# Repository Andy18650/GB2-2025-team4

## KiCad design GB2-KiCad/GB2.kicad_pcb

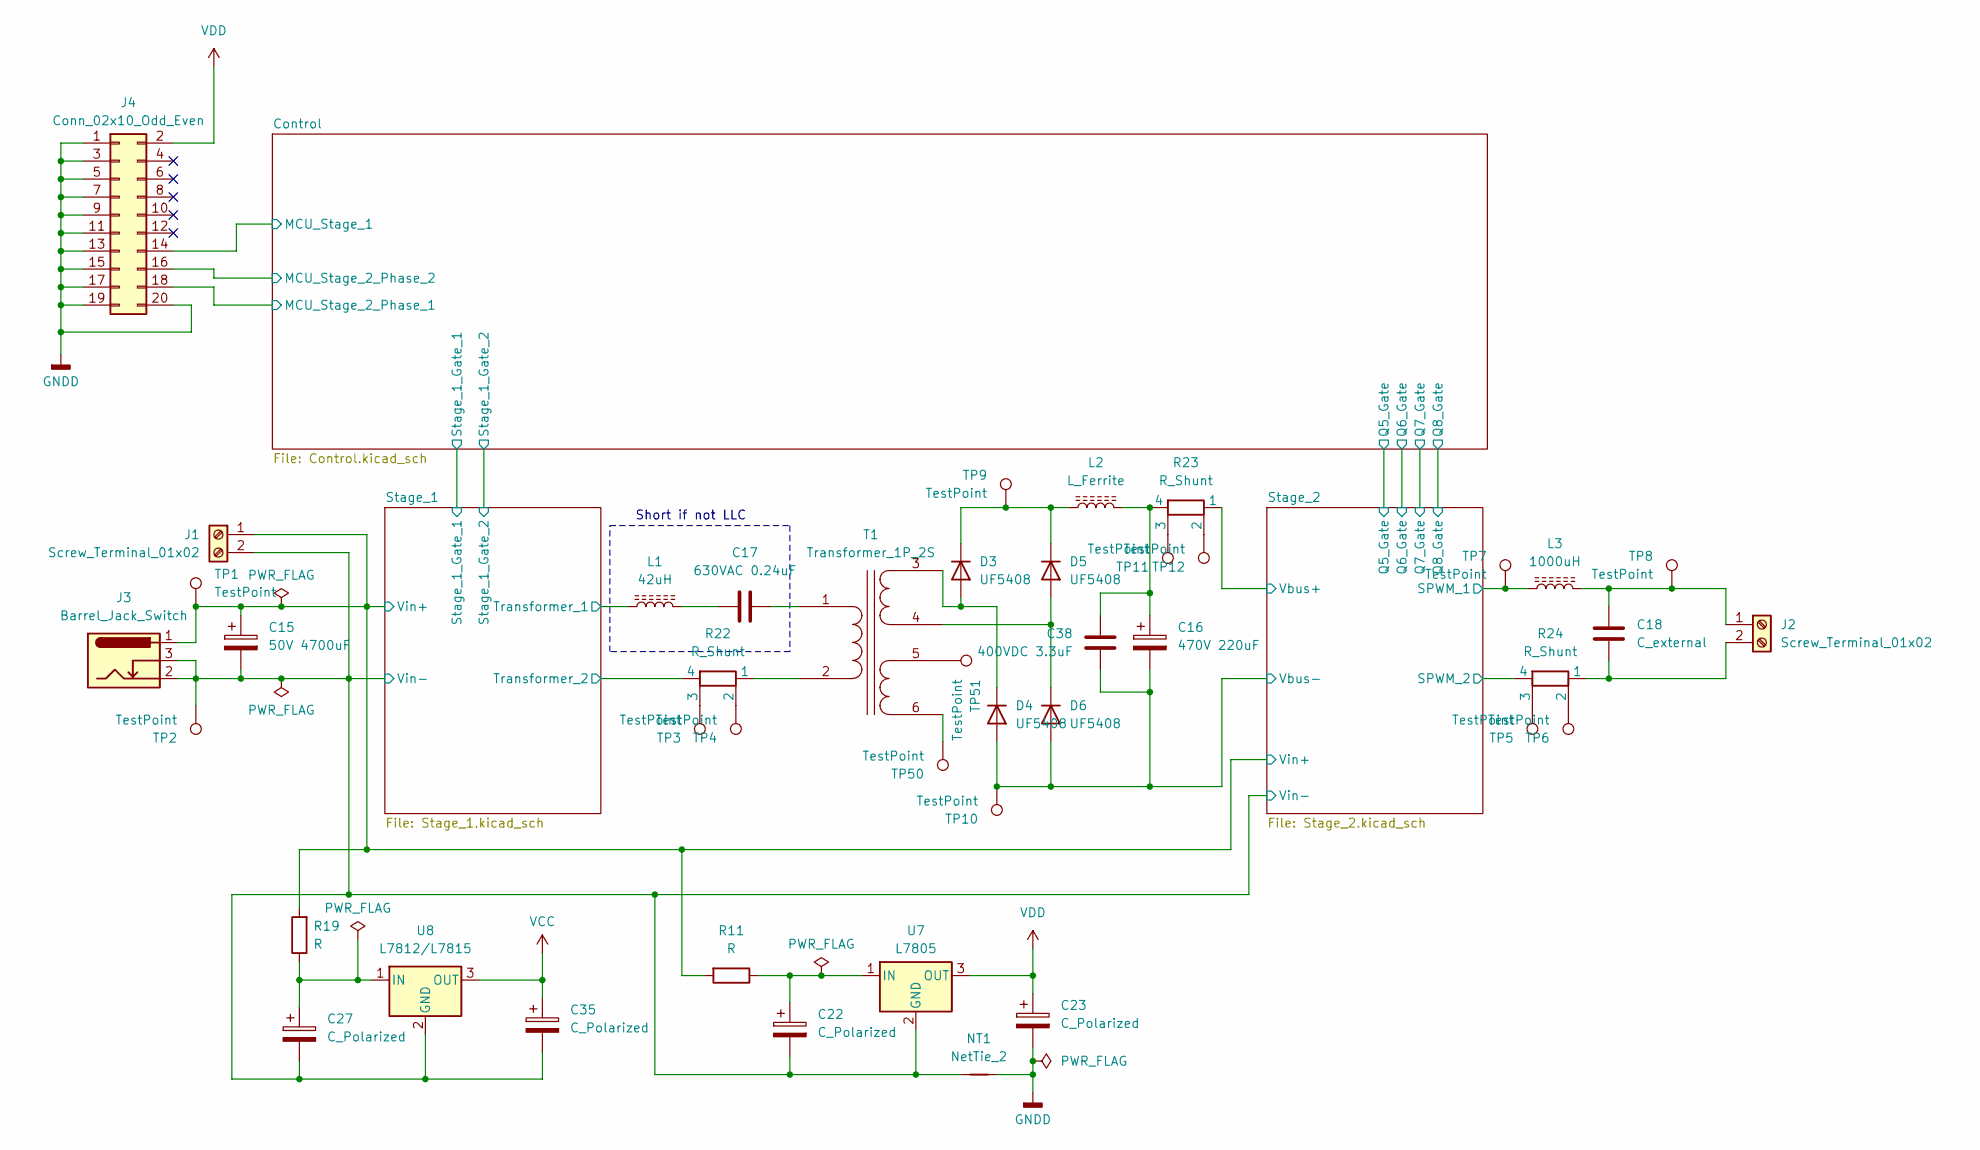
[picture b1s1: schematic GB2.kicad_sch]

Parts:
C15: 50V 4700uF; CP_Radial_D16.0mm_P7.50mm
C16: 470V 220uF; CP_Radial_D22.0mm_P10.00mm_SnapIn
C17: 630VAC 0.24uF; C_Rect_L33.0mm_W15.0mm_P27.50mm_MKS4
C18: C_external
C22, C23, C27, C35: C_Polarized; CP_Radial_D10.0mm_P2.50mm_P5.00mm
C38: 400VDC 3.3uF; C_Rect_L33.0mm_W15.0mm_P27.50mm_MKS4
D3, D4, D5, D6: UF5408; D_DO-201AD_P15.24mm_Horizontal
J1, J2: Screw_Terminal_01x02; TerminalBlock_Dinkle_DT-55-B01X-02_P10.00mm
J3: Barrel_Jack_Switch; BarrelJack_GCT_DCJ200-10-A_Horizontal
J4: Conn_02x10_Odd_Even; PinHeader_2x10_P2.54mm_Vertical
L1: 42uH; L_Toroid_Vertical_L21.6mm_W8.4mm_P8.38mm_Pulse_G
L2: L_Ferrite; L_Toroid_Vertical_L21.6mm_W8.4mm_P8.38mm_Pulse_G
L3: 1000uH; L_Toroid_Vertical_L21.6mm_W8.4mm_P8.38mm_Pulse_G
NT1: NetTie_2; NetTie-2_SMD_Pad2.0mm
R11, R19: R; R_Axial_DIN0204_L3.6mm_D1.6mm_P7.62mm_Horizontal
R22, R23, R24: R_Shunt; R_Axial_Shunt_L22.2mm_W8.0mm_PS14.30mm_P25.40mm
T1: Transformer_1P_2S; Transformer_GB2_Horizontal
TP1, TP2, TP3, TP4, TP5, TP6, TP7, TP8, TP9, TP10, TP11, TP12, TP50, TP51: TestPoint; Pin_D1.0mm_L10.0mm
U7: L7805; TO-220-3_Vertical
U8: L7812/L7815; TO-220-3_Vertical

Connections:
/Control/MCU_Stage_1: J4.14; also elsewhere on the board
/Control/MCU_Stage_2_Phase_1: J4.18; also elsewhere on the board
/Control/MCU_Stage_2_Phase_2: J4.16; also elsewhere on the board
/Stage_1/Transformer_1: L1.1; also elsewhere on the board
/Stage_1/Transformer_2: R22.4; also elsewhere on the board
/Stage_1/Vin+: C15.1, J1.1, J3.1, R11.2, R19.2, TP1.1; also elsewhere on the board
/Stage_1/Vin-: C15.2, C22.2, C27.2, C35.2, J1.2, J3.2, J3.3, NT1.1, TP2.1, U7.2 (GND), U8.2 (GND); also elsewhere on the board
/Stage_2/SPWM_1: L3.1, TP7.1; also elsewhere on the board
/Stage_2/SPWM_2: R24.4; also elsewhere on the board
/Stage_2/Vbus+: R23.1; also elsewhere on the board
/Stage_2/Vbus-: C16.2, C38.1, D4.2 (A), D6.2 (A), TP10.1; also elsewhere on the board
GNDD: C23.2, J4.1, J4.3, J4.5, J4.7, J4.9, J4.11, J4.13, J4.15, J4.17, J4.19, J4.20, NT1.2; also elsewhere on the board
unnamed: C16.1, C38.2, L2.2, R23.4
unnamed: C17.1, L1.2
unnamed: D3.2 (A), D4.1 (K), T1.3 (SA)
unnamed: D3.1 (K), D5.1 (K), L2.1, TP9.1
unnamed: D5.2 (A), D6.1 (K), T1.4 (SB)
unnamed: C18.2, J2.1, L3.2, TP8.1
unnamed: C18.1, J2.2, R24.1
unnamed: R22.2, TP4.1
unnamed: R22.3, TP3.1
unnamed: R23.2, TP12.1
unnamed: R23.3, TP11.1
unnamed: R24.2, TP6.1
unnamed: R24.3, TP5.1
unnamed: C17.2, T1.1 (AA)
unnamed: R22.1, T1.2 (AB)
unnamed: T1.5 (SC), TP51.1
unnamed: T1.6 (SD), TP50.1
unnamed: C22.1, R11.1, U7.1 (IN)
unnamed: C27.1, R19.1, U8.1 (IN)
VCC: C35.1, U8.3 (OUT); also elsewhere on the board
VDD: C23.1, J4.2, U7.3 (OUT); also elsewhere on the board

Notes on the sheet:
Short if not LLC

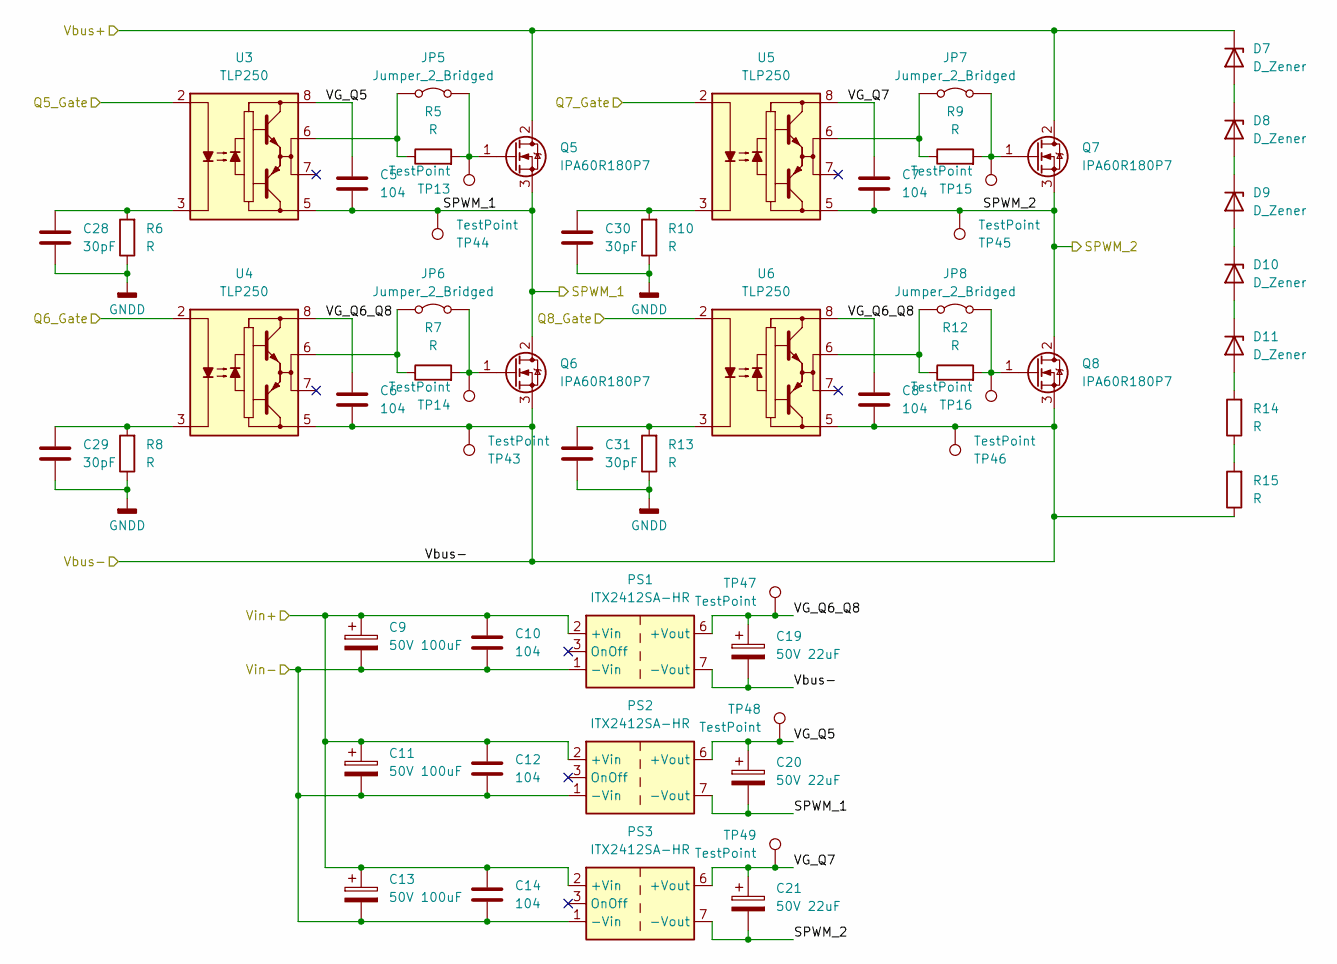
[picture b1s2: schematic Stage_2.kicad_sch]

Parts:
C5, C6, C7, C8, C10, C12, C14: 104; C_Disc_D7.0mm_W2.5mm_P5.00mm
C9, C11, C13: 50V 100uF; CP_Radial_D10.0mm_P2.50mm_P5.00mm
C19, C20, C21: 50V 22uF; CP_Radial_D5.0mm_P2.00mm
C28, C29, C30, C31: 30pF; C_Disc_D3.4mm_W2.1mm_P2.50mm
D7, D8, D9, D10, D11: D_Zener; D_DO-41_SOD81_P10.16mm_Horizontal
JP5, JP6, JP7, JP8: Jumper_2_Bridged; SolderJumper-2_P1.3mm_Bridged_Pad1.0x1.5mm
PS1, PS2, PS3: ITX2412SA-HR; Converter_DCDC_XP_POWER-ITxxxxxS_THT
Q5, Q6, Q7, Q8: IPA60R180P7; TO-220-3_Vertical
R5, R6, R7, R8, R9, R10, R12, R13, R14, R15: R; R_Axial_DIN0204_L3.6mm_D1.6mm_P7.62mm_Horizontal
TP13, TP14, TP15, TP16, TP43, TP44, TP45, TP46, TP47, TP48, TP49: TestPoint; Pin_D1.0mm_L10.0mm
U3, U4, U5, U6: TLP250; DIP-8_W7.62mm

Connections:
/Control/Q5_Gate: U3.2 (A); also elsewhere on the board
/Control/Q6_Gate: U4.2 (A); also elsewhere on the board
/Control/Q7_Gate: U5.2 (A); also elsewhere on the board
/Control/Q8_Gate: U6.2 (A); also elsewhere on the board
/Stage_1/Vin+: C9.1, C10.1, C11.1, C12.1, C13.1, C14.1, PS1.2 (+Vin), PS2.2 (+Vin), PS3.2 (+Vin); also elsewhere on the board
/Stage_1/Vin-: C9.2, C10.2, C11.2, C12.2, C13.2, C14.2, PS1.1 (-Vin), PS2.1 (-Vin), PS3.1 (-Vin); also elsewhere on the board
/Stage_2/SPWM_1: C5.2, C20.2, PS2.7 (-Vout), Q5.3 (S), Q6.2 (D), TP44.1, U3.5 (VEE); also elsewhere on the board
/Stage_2/SPWM_2: C7.2, C21.2, PS3.7 (-Vout), Q7.3 (S), Q8.2 (D), TP45.1, U5.5 (VEE); also elsewhere on the board
/Stage_2/VG_Q5: C5.1, C20.1, PS2.6 (+Vout), TP48.1, U3.8 (VCC)
/Stage_2/VG_Q6_Q8: C6.1, C8.1, C19.1, PS1.6 (+Vout), TP47.1, U4.8 (VCC), U6.8 (VCC)
/Stage_2/VG_Q7: C7.1, C21.1, PS3.6 (+Vout), TP49.1, U5.8 (VCC)
/Stage_2/Vbus+: D7.1 (K), Q5.2 (D), Q7.2 (D); also elsewhere on the board
/Stage_2/Vbus-: C6.2, C8.2, C19.2, PS1.7 (-Vout), Q6.3 (S), Q8.3 (S), R15.1, TP43.1, TP46.1, U4.5 (VEE), U6.5 (VEE); also elsewhere on the board
GNDD: C28.2, C29.2, C30.2, C31.2, R6.1, R8.1, R10.1, R13.1; also elsewhere on the board
unnamed: D7.2 (A), D8.1 (K)
unnamed: D8.2 (A), D9.1 (K)
unnamed: D10.2 (A), D11.1 (K)
unnamed: D9.2 (A), D10.1 (K)
unnamed: D11.2 (A), R14.2
unnamed: JP5.1 (A), R5.1, U3.6 (VO)
unnamed: JP5.2 (B), Q5.1 (G), R5.2, TP13.1
unnamed: JP6.1 (A), R7.1, U4.6 (VO)
unnamed: JP6.2 (B), Q6.1 (G), R7.2, TP14.1
unnamed: JP7.1 (A), R9.1, U5.6 (VO)
unnamed: JP7.2 (B), Q7.1 (G), R9.2, TP15.1
unnamed: JP8.1 (A), R12.1, U6.6 (VO)
unnamed: JP8.2 (B), Q8.1 (G), R12.2, TP16.1
unnamed: R14.1, R15.2
unnamed: C28.1, R6.2, U3.3 (C)
unnamed: C29.1, R8.2, U4.3 (C)
unnamed: C30.1, R10.2, U5.3 (C)
unnamed: C31.1, R13.2, U6.3 (C)

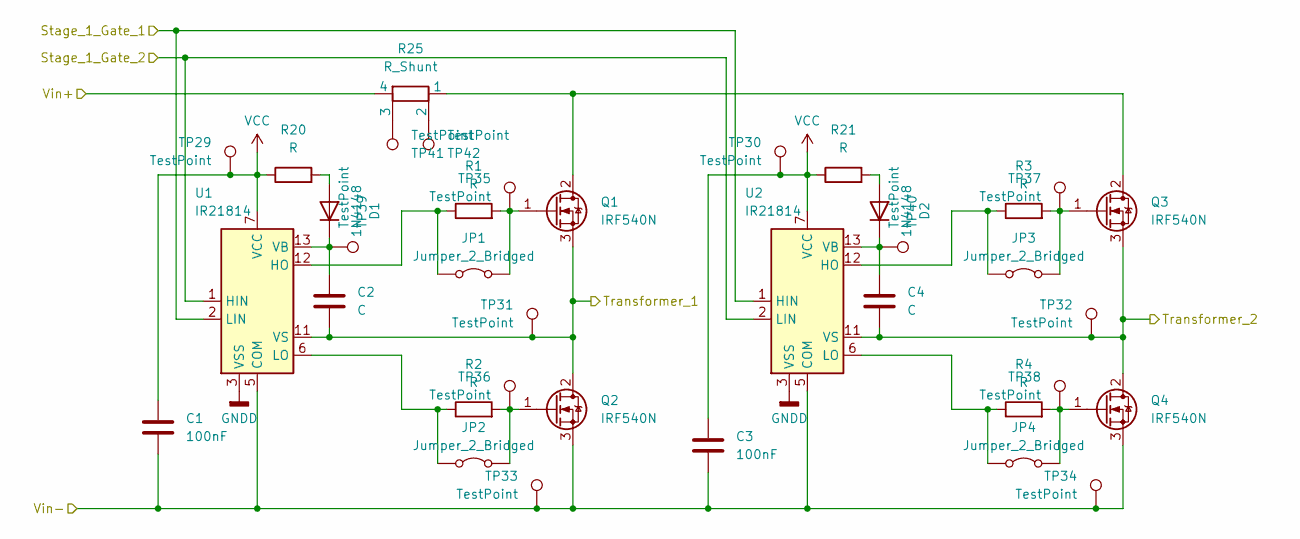
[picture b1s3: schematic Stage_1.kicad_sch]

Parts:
C1, C3: 100nF; C_Disc_D7.0mm_W2.5mm_P5.00mm
C2, C4: C; C_Disc_D7.0mm_W2.5mm_P5.00mm
D1, D2: 1N4148; D_DO-35_SOD27_P10.16mm_Horizontal
JP1, JP2, JP3, JP4: Jumper_2_Bridged; SolderJumper-2_P1.3mm_Bridged_Pad1.0x1.5mm
Q1, Q2, Q3, Q4: IRF540N; TO-220-3_Vertical
R1, R2, R3, R4, R20, R21: R; R_Axial_DIN0204_L3.6mm_D1.6mm_P7.62mm_Horizontal
R25: R_Shunt; R_Axial_Shunt_L22.2mm_W8.0mm_PS14.30mm_P25.40mm
TP29, TP30, TP31, TP32, TP33, TP34, TP35, TP36, TP37, TP38, TP39, TP40, TP41, TP42: TestPoint; Pin_D1.0mm_L10.0mm
U1, U2: IR21814; DIP-14_W7.62mm_Socket

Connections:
/Control/Stage_1_Gate_1: U1.2 (LIN), U2.1 (HIN); also elsewhere on the board
/Control/Stage_1_Gate_2: U1.1 (HIN), U2.2 (LIN); also elsewhere on the board
/Stage_1/Transformer_1: C2.2, Q1.3 (S), Q2.2 (D), TP31.1, U1.11 (VS); also elsewhere on the board
/Stage_1/Transformer_2: C4.2, Q3.3 (S), Q4.2 (D), TP32.1, U2.11 (VS); also elsewhere on the board
/Stage_1/Vin+: R25.4; also elsewhere on the board
/Stage_1/Vin-: C1.2, C3.2, Q2.3 (S), Q4.3 (S), TP33.1, TP34.1, U1.5 (COM), U2.5 (COM); also elsewhere on the board
GNDD: U1.3 (VSS), U2.3 (VSS); also elsewhere on the board
unnamed: D1.2 (A), R20.2
unnamed: C2.1, D1.1 (K), TP39.1, U1.13 (VB)
unnamed: D2.2 (A), R21.2
unnamed: C4.1, D2.1 (K), TP40.1, U2.13 (VB)
unnamed: JP1.1 (A), R1.1, U1.12 (HO)
unnamed: JP1.2 (B), Q1.1 (G), R1.2, TP35.1
unnamed: JP2.1 (A), R2.1, U1.6 (LO)
unnamed: JP2.2 (B), Q2.1 (G), R2.2, TP36.1
unnamed: JP3.1 (A), R3.1, U2.12 (HO)
unnamed: JP3.2 (B), Q3.1 (G), R3.2, TP37.1
unnamed: JP4.1 (A), R4.1, U2.6 (LO)
unnamed: JP4.2 (B), Q4.1 (G), R4.2, TP38.1
unnamed: Q1.2 (D), Q3.2 (D), R25.1
unnamed: R25.2, TP42.1
unnamed: R25.3, TP41.1
VCC: C1.1, C3.1, R20.1, R21.1, TP29.1, TP30.1, U1.7 (VCC), U2.7 (VCC); also elsewhere on the board

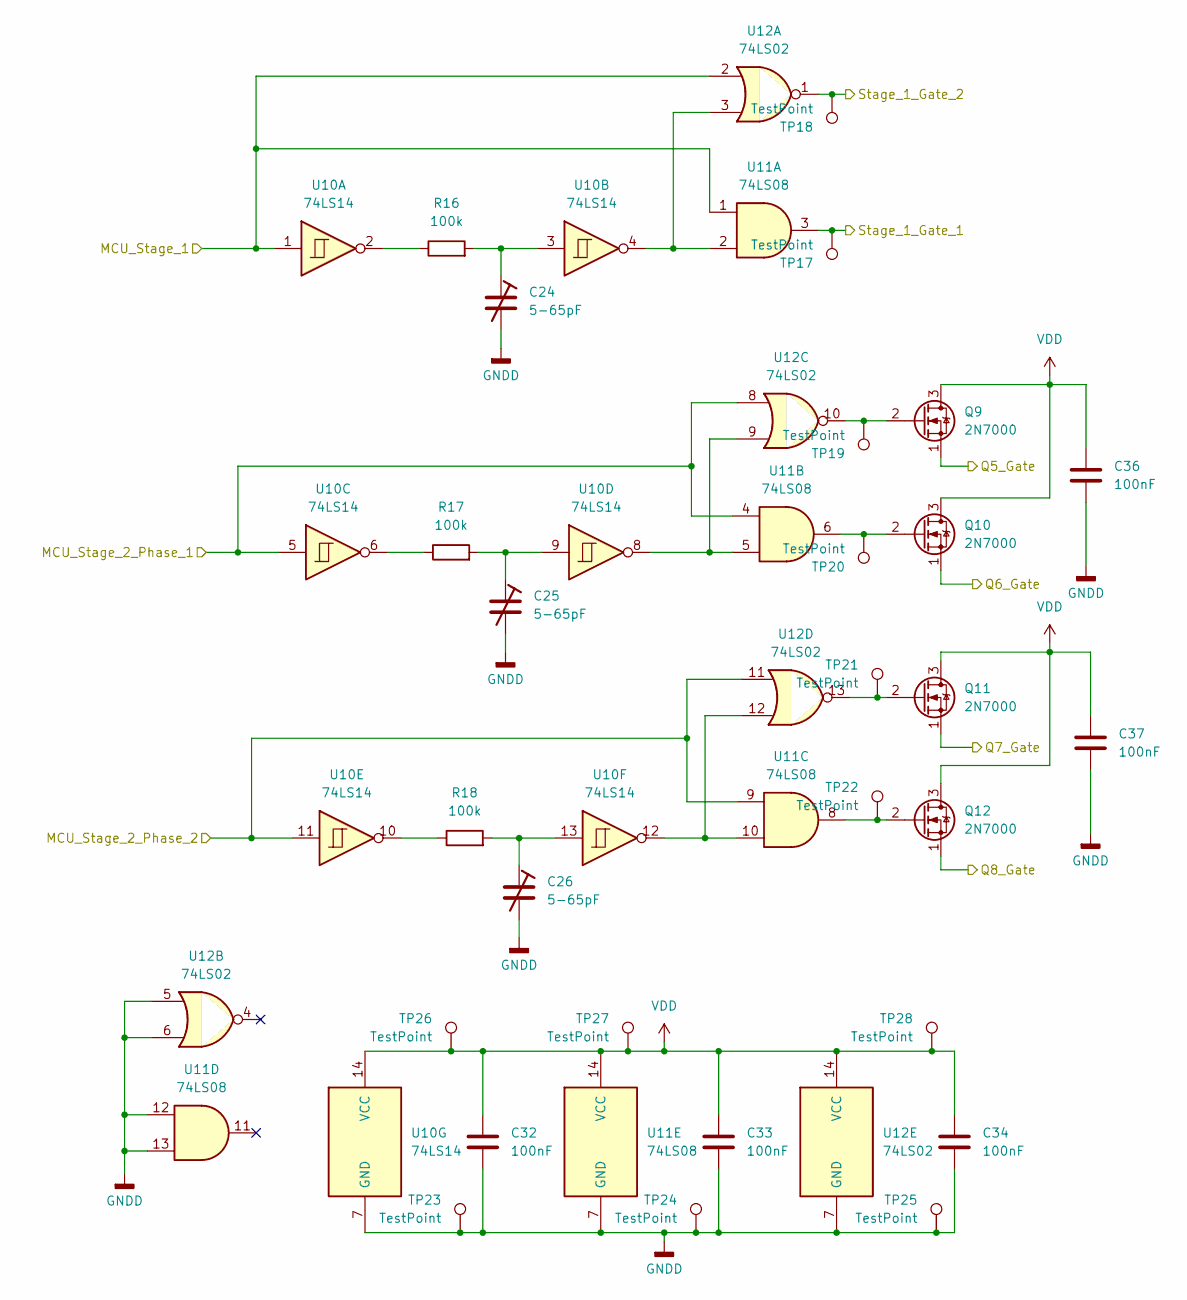
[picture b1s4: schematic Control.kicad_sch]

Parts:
C24, C25, C26: 5-65pF; C_Trim
C32, C33, C34, C36, C37: 100nF; C_Disc_D7.0mm_W2.5mm_P5.00mm
Q9, Q10, Q11, Q12: 2N7000; TO-92L_HandSolder
R16, R17, R18: 100k; R_Axial_DIN0204_L3.6mm_D1.6mm_P7.62mm_Horizontal
TP17, TP18, TP19, TP20, TP21, TP22, TP23, TP24, TP25, TP26, TP27, TP28: TestPoint; Pin_D1.0mm_L10.0mm
U10: 74LS14; DIP-14_W7.62mm_Socket
U11: 74LS08; DIP-14_W7.62mm_Socket
U12: 74LS02; DIP-14_W7.62mm_Socket

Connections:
/Control/MCU_Stage_1: U10.1, U11.1, U12.2; also elsewhere on the board
/Control/MCU_Stage_2_Phase_1: U10.5, U11.4, U12.8; also elsewhere on the board
/Control/MCU_Stage_2_Phase_2: U10.11, U11.9, U12.11; also elsewhere on the board
/Control/Q5_Gate: Q9.1 (S); also elsewhere on the board
/Control/Q6_Gate: Q10.1 (S); also elsewhere on the board
/Control/Q7_Gate: Q11.1 (S); also elsewhere on the board
/Control/Q8_Gate: Q12.1 (S); also elsewhere on the board
/Control/Stage_1_Gate_1: TP17.1, U11.3; also elsewhere on the board
/Control/Stage_1_Gate_2: TP18.1, U12.1; also elsewhere on the board
GNDD: C24.2, C25.2, C26.2, C32.2, C33.2, C34.2, C36.2, C37.2, TP23.1, TP24.1, TP25.1, U10.7 (GND), U11.7 (GND), U11.12, U11.13, U12.5, U12.6, U12.7 (GND); also elsewhere on the board
unnamed: C24.1, R16.2, U10.3
unnamed: C25.1, R17.2, U10.9
unnamed: C26.1, R18.2, U10.13
unnamed: Q9.2 (G), TP19.1, U12.10
unnamed: Q10.2 (G), TP20.1, U11.6
unnamed: Q11.2 (G), TP21.1, U12.13
unnamed: Q12.2 (G), TP22.1, U11.8
unnamed: R16.1, U10.2
unnamed: R17.1, U10.6
unnamed: R18.1, U10.10
unnamed: U10.4, U11.2, U12.3
unnamed: U10.8, U11.5, U12.9
unnamed: U10.12, U11.10, U12.12
VDD: C32.1, C33.1, C34.1, C36.1, C37.1, Q9.3 (D), Q10.3 (D), Q11.3 (D), Q12.3 (D), TP26.1, TP27.1, TP28.1, U10.14 (VCC), U11.14 (VCC), U12.14 (VCC); also elsewhere on the board

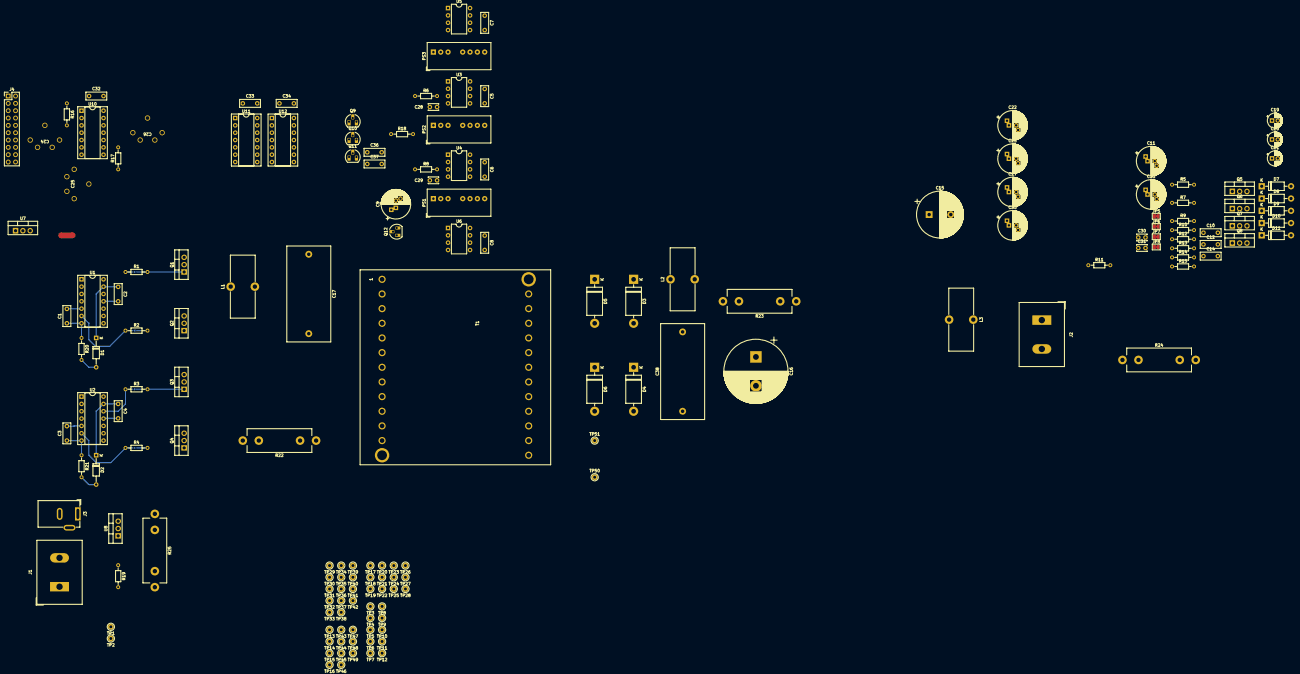
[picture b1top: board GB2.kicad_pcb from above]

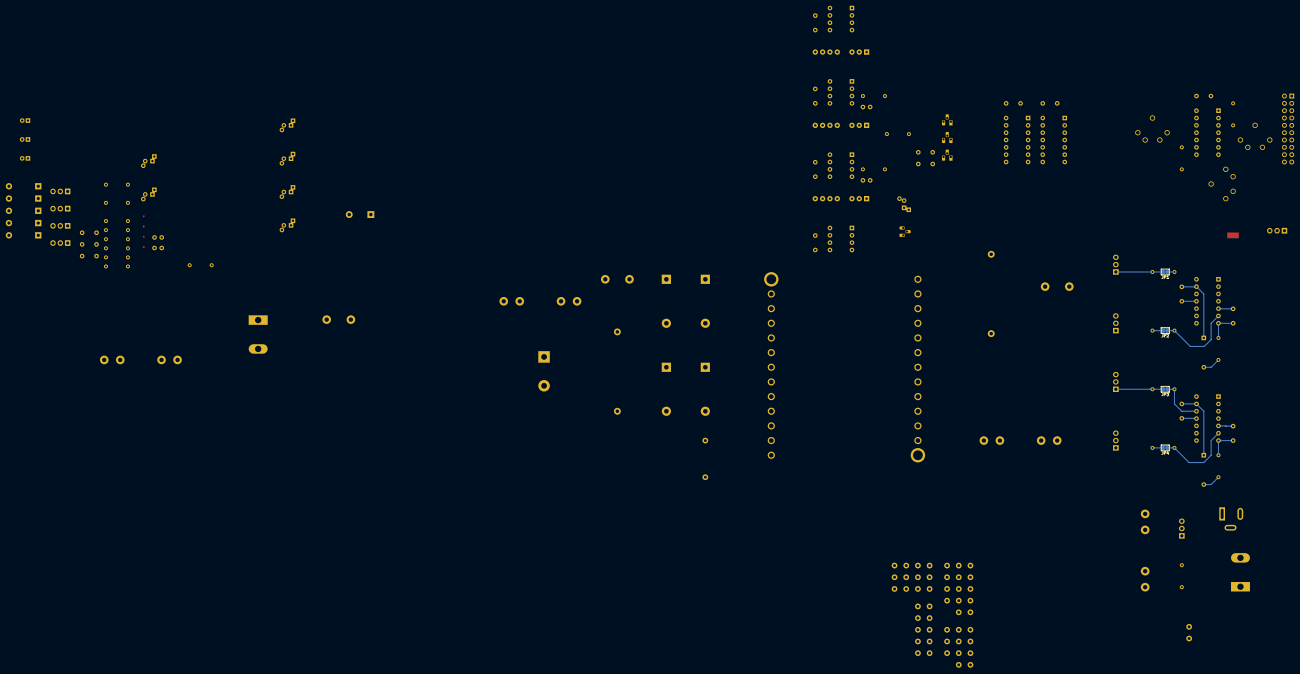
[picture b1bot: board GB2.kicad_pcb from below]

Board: 2 copper layers, 167 parts (4 on the bottom side), 88 nets.

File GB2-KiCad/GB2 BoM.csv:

"Reference","Value","Datasheet","Footprint","Qty","DNP"
"C1,C3,C32,C33,C34,C36,C37","100nF","~","Capacitor_THT:C_Disc_D7.0mm_W2.5mm_P5.00mm","7",""
"C2,C4","C","~","Capacitor_THT:C_Disc_D7.0mm_W2.5mm_P5.00mm","2",""
"C5,C6,C7,C8,C10,C12,C14","104","~","Capacitor_THT:C_Disc_D7.0mm_W2.5mm_P5.00mm","7",""
"C9,C11,C13","50V 100uF","~","Capacitor_THT:CP_Radial_D10.0mm_P2.50mm_P5.00mm","3",""
"C15","50V 4700uF","~","Capacitor_THT:CP_Radial_D16.0mm_P7.50mm","1",""
"C16","470V 220uF","~","Capacitor_THT:CP_Radial_D22.0mm_P10.00mm_SnapIn","1",""
"C18","C_external","~","","1",""
"C19,C20,C21","50V 22uF","~","Capacitor_THT:CP_Radial_D5.0mm_P2.00mm","3",""
"C22,C23,C27,C35","C_Polarized","~","Capacitor_THT:CP_Radial_D10.0mm_P2.50mm_P5.00mm","4",""
"C24,C25,C26","5-65pF","https://www.farnell.com/datasheets/3868946.pdf","GB2:C_Trim","3",""
"C28,C29,C30,C31","30pF","~","Capacitor_THT:C_Disc_D3.4mm_W2.1mm_P2.50mm","4",""
"C38","400VDC 3.3uF","~","Capacitor_THT:C_Rect_L33.0mm_W15.0mm_P27.50mm_MKS4","1",""
"D1,D2","1N4148","https://assets.nexperia.com/documents/data-sheet/1N4148_1N4448.pdf","Diode_THT:D_DO-35_SOD27_P10.16mm_Horizontal","2",""
"D3,D4,D5,D6","UF5408","http://www.vishay.com/docs/88756/uf5400.pdf","Diode_THT:D_DO-201AD_P15.24mm_Horizontal","4",""
"J1,J2","Screw_Terminal_01x02","~","TerminalBlock_Dinkle:TerminalBlock_Dinkle_DT-55-B01X-02_P10.00mm","2",""
"J3","Barrel_Jack_Switch","~","Connector_BarrelJack:BarrelJack_GCT_DCJ200-10-A_Horizontal","1",""
"J4","Conn_02x10_Odd_Even","~","Connector_PinHeader_2.54mm:PinHeader_2x10_P2.54mm_Vertical","1",""
"L2","L_Ferrite","~","Inductor_THT:L_Toroid_Vertical_L21.6mm_W8.4mm_P8.38mm_Pulse_G","1",""
"L3","1000uH","~","Inductor_THT:L_Toroid_Vertical_L21.6mm_W8.4mm_P8.38mm_Pulse_G","1",""
"NT1","NetTie_2","~","NetTie:NetTie-2_SMD_Pad2.0mm","1",""
"PS1,PS2,PS3","ITX2412SA-HR","https://www.xppower.com/pdfs/SF_ITX.pdf","Converter_DCDC:Converter_DCDC_XP_POWER-ITxxxxxS_THT","3",""
"Q1,Q2,Q3,Q4","IRF540N","http://www.irf.com/product-info/datasheets/data/irf540n.pdf","Package_TO_SOT_THT:TO-220-3_Vertical","4",""
"Q5,Q6,Q7,Q8","IPA60R180P7","https://www.vle.cam.ac.uk/pluginfile.php/5112411/mod_folder/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","Package_TO_SOT_THT:TO-220-3_Vertical","4",""
"Q9,Q10,Q11,Q12","2N7000","https://www.vishay.com/docs/70226/70226.pdf","Package_TO_SOT_THT:TO-92L_HandSolder","4",""
"R1,R2,R3,R4,R5,R6,R7,R8,R9,R10,R11,R12,R13,R19,R20,R21","R","~","Resistor_THT:R_Axial_DIN0204_L3.6mm_D1.6mm_P7.62mm_Horizontal","16",""
"R16,R17,R18","100k","~","Resistor_THT:R_Axial_DIN0204_L3.6mm_D1.6mm_P7.62mm_Horizontal","3",""
"R22,R23,R24,R25","R_Shunt","~","Resistor_THT:R_Axial_Shunt_L22.2mm_W8.0mm_PS14.30mm_P25.40mm","4",""
"T1","Transformer_1P_2S","~","GB2:Transformer_GB2_Horizontal","1",""
"TP1,TP2,TP3,TP4,TP5,TP6,TP7,TP8,TP9,TP10,TP11,TP12,TP13,TP14,TP15,TP16,TP17,TP18,TP19,TP20,TP21,TP22,TP23,TP24,TP25,TP26,TP27,TP28,TP29,TP30,TP31,TP32,TP33,TP34,TP35,TP36,TP37,TP38,TP39,TP40,TP41,TP42,TP43,TP44,TP45,TP46,TP47,TP48,TP49,TP50,TP51","TestPoint","~","Connector_Pin:Pin_D1.0mm_L10.0mm","51",""
"U1,U2","IR21814","https://www.infineon.com/dgdl/ir2181.pdf?fileId=5546d4625336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","Package_DIP:DIP-14_W7.62mm_Socket","2",""
"U3,U4,U5,U6","TLP250","http://toshiba.semicon-storage.com/info/docget.jsp?did=16821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","Package_DIP:DIP-8_W7.62mm","4",""
"U7","L7805","http://www.st.com/content/ccc/resource/technical/document/da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","Package_TO_SOT_THT:TO-220-3_Vertical","1",""
"U8","L7812/L7815","http://www.st.com/content/ccc/resource/technical/document/da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","Package_TO_SOT_THT:TO-220-3_Vertical","1",""
"U10","74LS14","http://www.ti.com/lit/gpn/sn74LS14","Package_DIP:DIP-14_W7.62mm_Socket","1",""
"U11","74LS08","http://www.ti.com/lit/gpn/sn74LS08","Package_DIP:DIP-14_W7.62mm_Socket","1",""
"U12","74LS02","http://www.ti.com/lit/gpn/sn74ls02","Package_DIP:DIP-14_W7.62mm_Socket","1",""

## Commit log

2025-05-17 Complete schematic
    Initialized the repository with completed KiCad schematic and placeholders for other parts of the project.
2025-05-19 Added shunts and test points
    Added shunt resistors and test points to the PCB for debugging purposes.
2025-05-20 Update GB2-KiCad and add GB2-PLECS folder
2025-05-21 GB2-KiCad Preliminary layout design updated wih actual PCB mod
2025-05-23 Full pcb layout update
